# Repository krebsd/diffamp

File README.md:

# Differential Amplifier - diffamp

Differential Amplifier circuit for use for example in current sensing applications. The circuit is designed to be used in conjunction with an oscilloscope.

## PREFACE
This project and especially its documentation including this README is still in a very early state of development. This document will be updated with further information in the future.

## EDA

* [KiCad](http://kicad-pcb.org) - KiCad EDA is used for the PCB design

## Authors

* **David Krebs** - *Initial work* - [krebsd](https://github.com/krebsd)

## License

<br />This work is licensed under a <a rel="license" href="http://creativecommons.org/licenses/by-sa/4.0/">Creative Commons Attribution-ShareAlike 4.0 International License</a>

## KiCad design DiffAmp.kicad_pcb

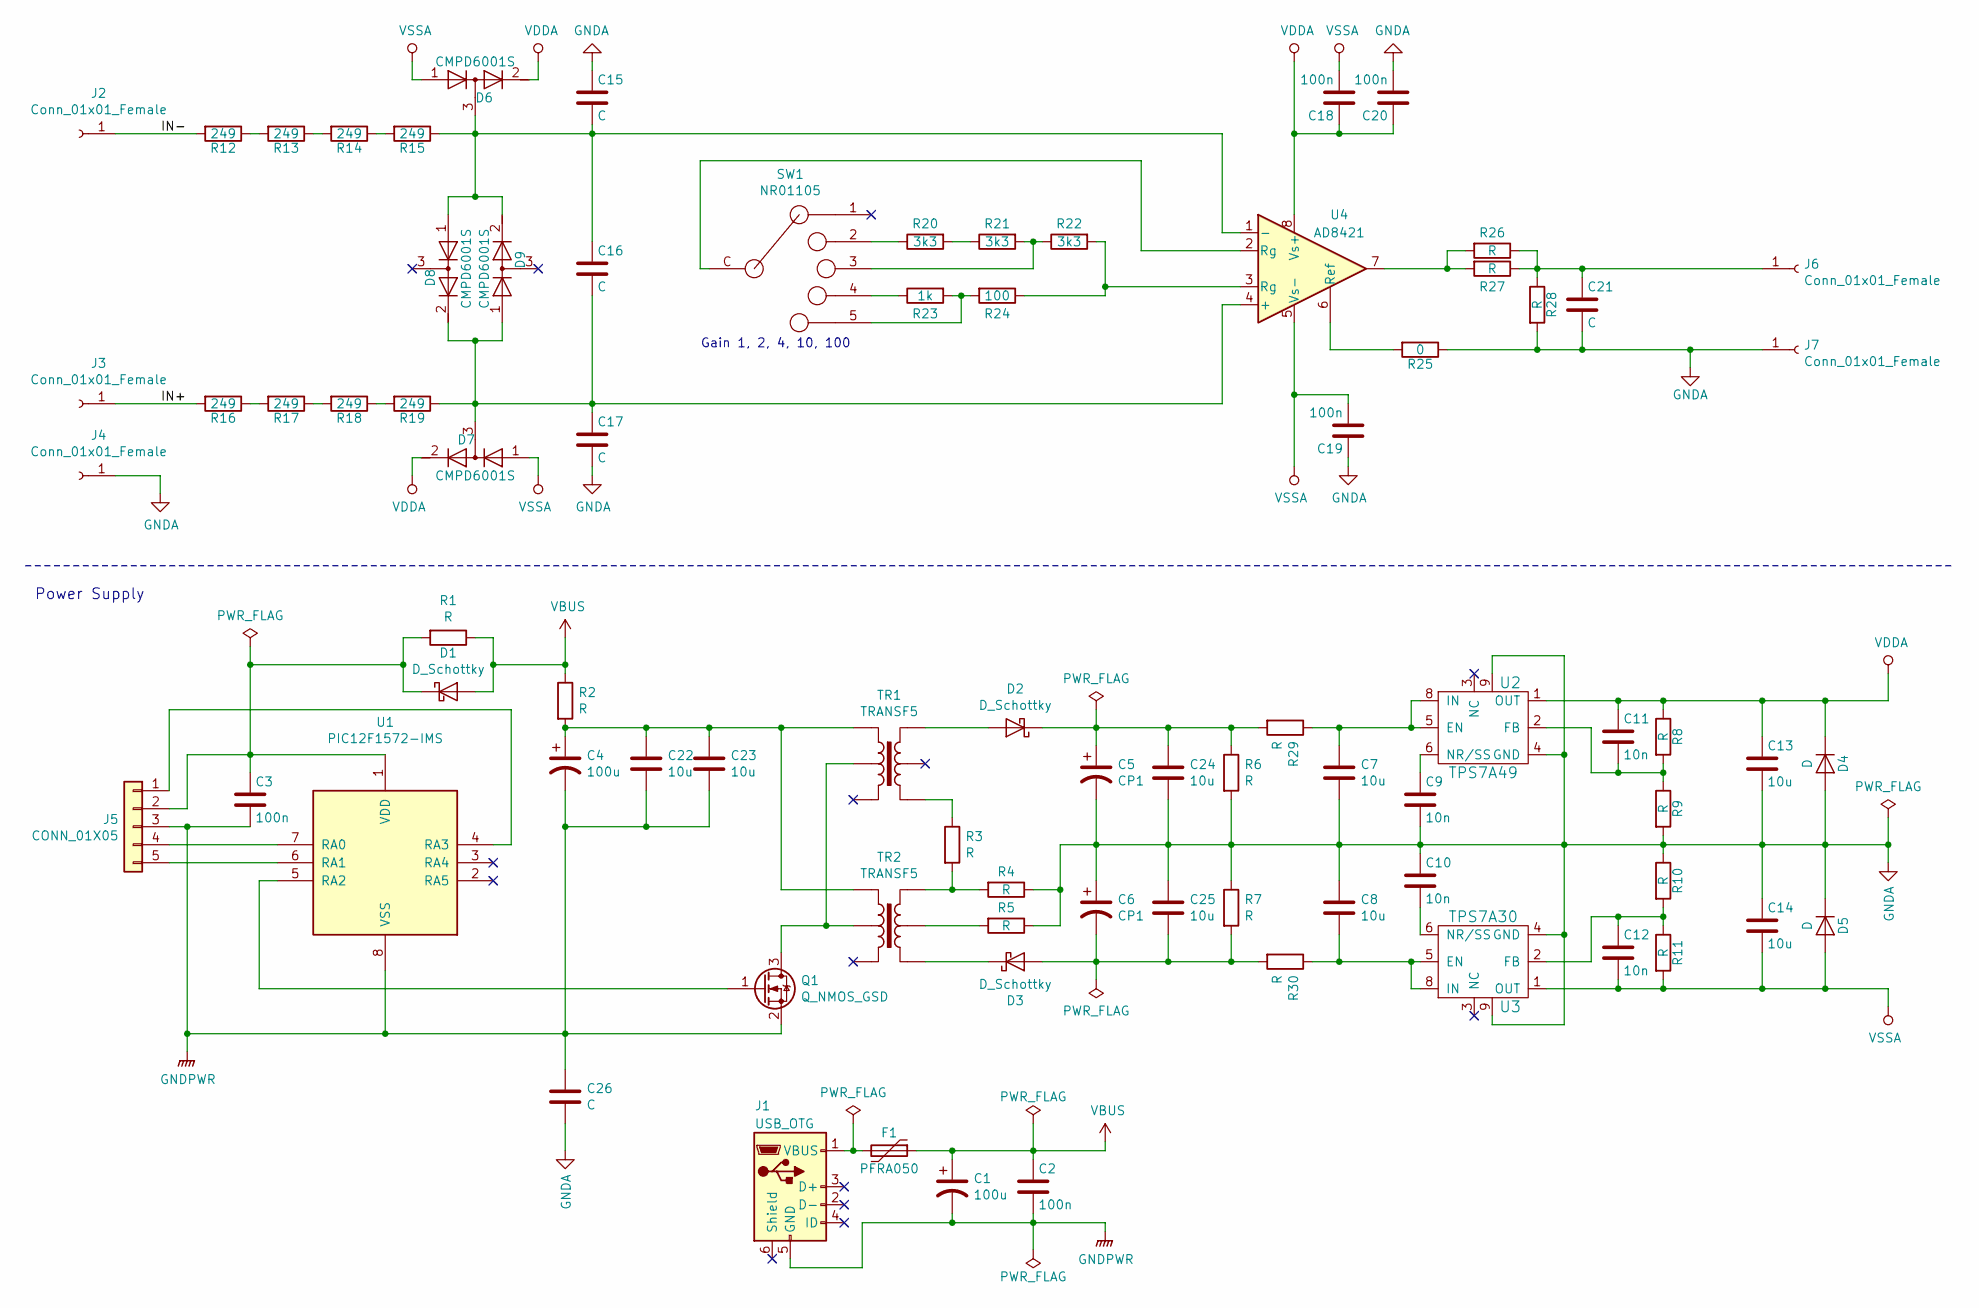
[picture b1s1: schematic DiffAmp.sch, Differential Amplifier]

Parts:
C1, C4: 100u; CP_Radial_D8.0mm_P3.50mm
C2, C3, C18, C19, C20: 100n; C_0805
C5, C6: CP1; CP_Radial_D8.0mm_P3.50mm
C7, C8, C22, C23, C24, C25: 10u; C_1210_3225Metric
C9, C10, C11, C12: 10n; C_0805
C13, C14: 10u; C_1210
C15, C16, C17, C21: C; C_0805
C26: C; C_0805_2012Metric
D1, D2, D3: D_Schottky; D_MiniMELF
D4, D5: D; D_MiniMELF
D6, D7, D8, D9: CMPD6001S; SOT-23
F1: PFRA050; R_Axial_DIN0204_L3.6mm_D1.6mm_P5.08mm_Horizontal
J1: USB_OTG; MIC_USB_BBU
J2, J3, J4, J6, J7: Conn_01x01_Female; PB4
J5: CONN_01X05; Pin_Header_Straight_1x05_Pitch2.54mm
Q1: Q_NMOS_GSD; SOT-23
R1, R2, R3, R4, R5, R29, R30: R; R_0805_SolderJumper
R6, R7, R8, R9, R10, R11, R26, R27, R28: R; R_0805
R12, R13, R14, R15, R16, R17, R18, R19: 249; R_0805
R20, R21, R22: 3k3; R_0805
R23: 1k; R_0805
R24: 100; R_0805
R25: 0; R_0805_SolderJumper
SW1: NR01105; NKK_NR01
TR1, TR2: TRANSF5; Würth_7603900XX
U1: PIC12F1572-IMS; MSOP-8_3x3mm_Pitch0.65mm
U2: TPS7A49; MSOP-8-1EP_3x3mm_Pitch0.65mm
U3: TPS7A30; MSOP-8-1EP_3x3mm_Pitch0.65mm
U4: AD8421; SOIC-8_3.9x4.9mm_Pitch1.27mm

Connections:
/IN+: J3.1, R16.2
/IN-: J2.1, R12.2
GNDA: C5.2, C6.1, C7.2, C8.1, C9.2, C10.1, C13.2, C14.1, C15.1, C17.2, C19.1, C20.2, C21.2, C24.2, C25.1, C26.1, D4.2 (A), D5.1 (K), J4.1, J7.1, R4.1, R5.1, R6.2, R7.1, R9.2, R10.1, R25.1, R28.2, U2.4 (GND), U2.9, U3.4 (GND), U3.9
GNDPWR: C1.2, C2.2, C3.2, C4.2, C22.2, C23.2, C26.2, J1.5 (GND), J5.3, Q1.2 (S), U1.8 (VSS)
unnamed: C3.1, D1.1 (K), J5.2, R1.2, U1.1 (VDD)
unnamed: C7.1, R29.1, U2.5 (EN), U2.8 (IN)
unnamed: C8.2, R30.1, U3.5 (EN), U3.8 (IN)
unnamed: C9.1, U2.6 (NR/SS)
unnamed: C10.2, U3.6 (NR/SS)
unnamed: C11.2, R8.2, R9.1, U2.2 (FB)
unnamed: C12.1, R10.2, R11.1, U3.2 (FB)
unnamed: C15.2, C16.1, D6.3 (common), D8.1 (A), D9.2 (K), R15.1, U4.1 (-)
unnamed: C16.2, C17.1, D7.3 (common), D8.2 (K), D9.1 (A), R19.1, U4.4 (+)
unnamed: C21.1, J6.1, R26.1, R27.1, R28.1
unnamed: C4.1, C22.1, C23.1, R2.2, TR1.1, TR2.1
unnamed: C5.1, C24.1, D2.1 (K), R6.1, R29.2
unnamed: C6.2, C25.2, D3.2 (A), R7.2, R30.2
unnamed: D2.2 (A), TR1.6
unnamed: D3.1 (K), TR2.4
unnamed: F1.2, J1.1 (VBUS)
unnamed: J5.1, U1.4 (RA3)
unnamed: J5.4, U1.7 (RA0)
unnamed: J5.5, U1.6 (RA1)
unnamed: Q1.1 (G), U1.5 (RA2)
unnamed: Q1.3 (D), TR1.2, TR2.2
unnamed: R3.1, TR1.4
unnamed: R3.2, R4.2, TR2.6
unnamed: R5.2, TR2.5
unnamed: R12.1, R13.2
unnamed: R13.1, R14.2
unnamed: R14.1, R15.2
unnamed: R16.1, R17.2
unnamed: R17.1, R18.2
unnamed: R18.1, R19.2
unnamed: R20.1, SW1.2
unnamed: R20.2, R21.1
unnamed: R21.2, R22.1, SW1.3
unnamed: R22.2, R24.1, U4.3 (Rg)
unnamed: R23.1, SW1.4
unnamed: R23.2, R24.2, SW1.5
unnamed: R25.2, U4.6 (Ref)
unnamed: R26.2, R27.2, U4.7
unnamed: SW1.C, U4.2 (Rg)
VBUS: C1.1, C2.1, D1.2 (A), F1.1, R1.1, R2.1
VDDA: C11.1, C13.1, C18.1, C20.1, D4.1 (K), D6.2 (K), D7.2 (K), R8.1, U2.1 (OUT), U4.8 (Vs+)
VSSA: C12.2, C14.2, C18.2, C19.2, D5.2 (A), D6.1 (A), D7.1 (A), R11.2, U3.1 (OUT), U4.5 (Vs-)

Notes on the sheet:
Power Supply
Gain 1, 2, 4, 10, 100

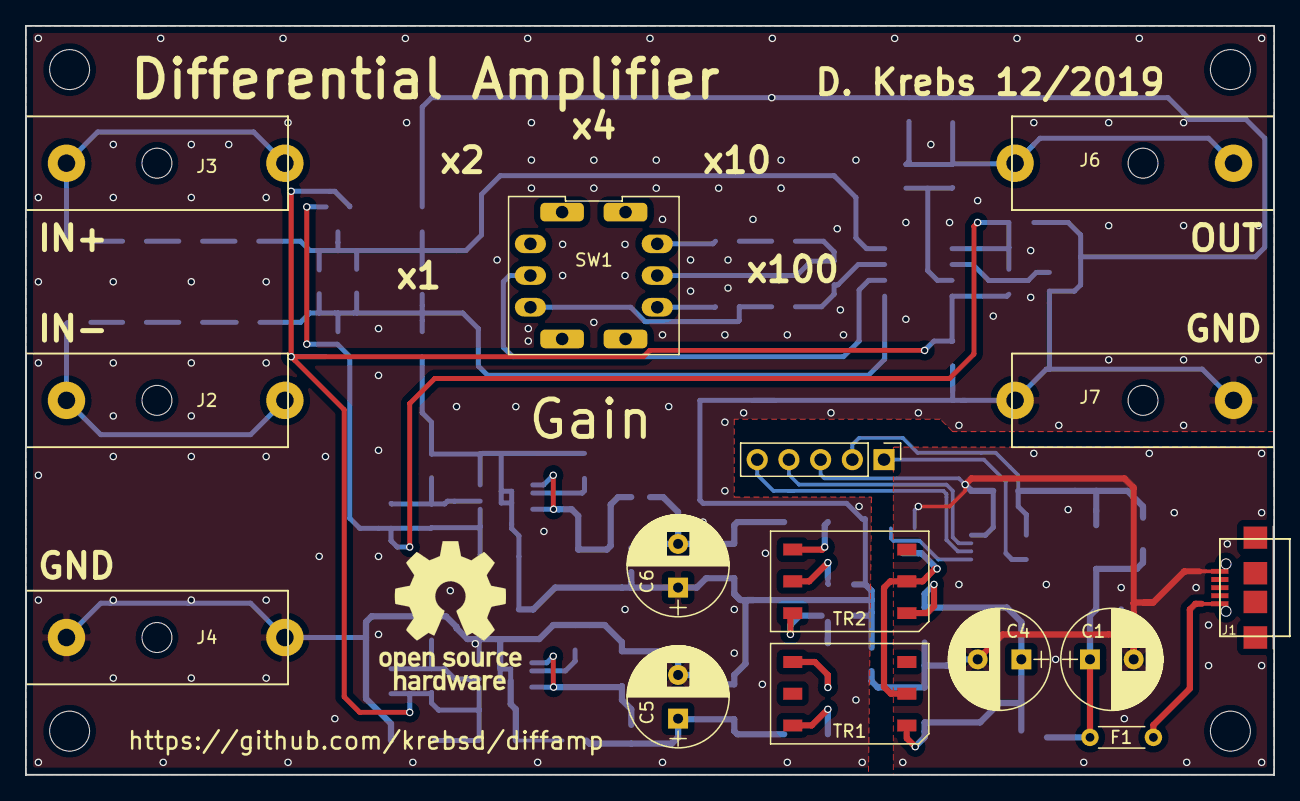
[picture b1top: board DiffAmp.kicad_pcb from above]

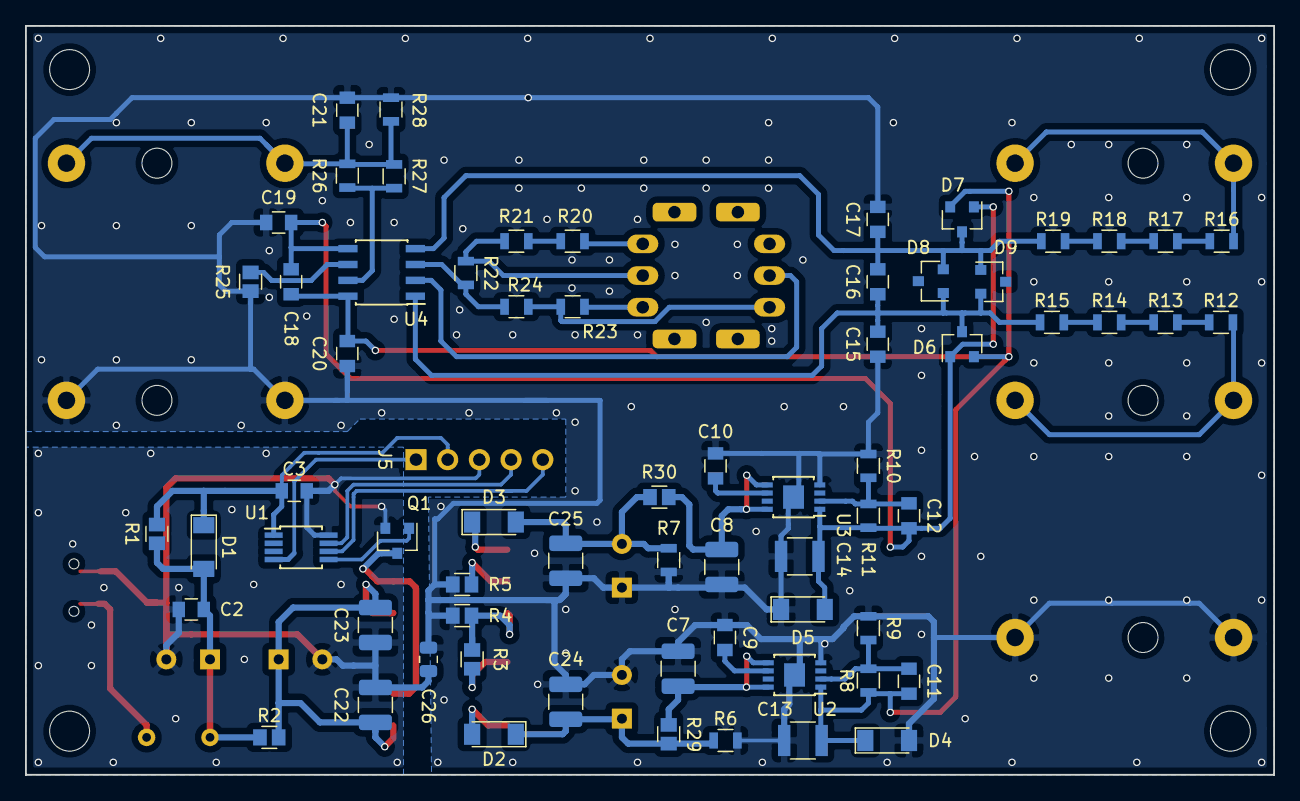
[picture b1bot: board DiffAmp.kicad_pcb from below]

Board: 2 copper layers, 100.0 x 60.0 mm, 81 parts (66 on the bottom side), 46 nets.

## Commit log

2019-12-11 Initial commit, README.md added
2019-12-11 LICENSE added
2019-12-11 Commit of KiCad Project including used footprints
2019-12-11 Added preliminary pdf-schematic
2019-12-16 Changes in first assembly added to schematic
2019-12-17 Schematic revised - change in negative supply voltage
